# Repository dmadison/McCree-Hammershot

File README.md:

## Synopsis
These are the associated files for my McCree Hammershot controller project! I turned a Nerf revolver into a custom controller for the character of [McCree](https://playoverwatch.com/en-us/heroes/mccree/) in *Overwatch*. The revolver contains an Arduino Pro Micro, an MPU-6050 IMU, and a host of other parts to handle McCree's controls. When paired with either a DDR dance pad or a Wii Nunchuk to handle his movement, I can use all of McCree's controls and play the game reasonably well.

For more information, check out the full build log on [PartsNotIncluded.com](http://www.partsnotincluded.com/projects/mccree-hammershot-controller/).

## Dependencies
The Hammershot program is dependent on the [CapacitiveSensor](https://github.com/PaulStoffregen/CapacitiveSensor/releases/tag/0.5.1), [Encoder](https://github.com/PaulStoffregen/Encoder/releases/tag/1.4.1) and [FastLED](https://github.com/FastLED/FastLED/releases/tag/v3.1.6) libraries. The Nunchuk code is dependent on the [WiiChuck](https://github.com/madhephaestus/WiiChuck/releases/tag/0.0.23) library to handle communication between the board and the Nunchuk. Both sketches are dependent on the Arduino IDE's built-in Keyboard, Mouse, and Wire libraries. The sketches were compiled using version 1.8.2 of the IDE.

I've linked to the specific library releases that work with this code. Note that future versions may not be compatible.

## License
The Arduino code, CAD files, and breakout PCB are licensed under the terms of the [GNU General Public License v3.0](https://www.gnu.org/licenses/gpl-3.0.en.html).

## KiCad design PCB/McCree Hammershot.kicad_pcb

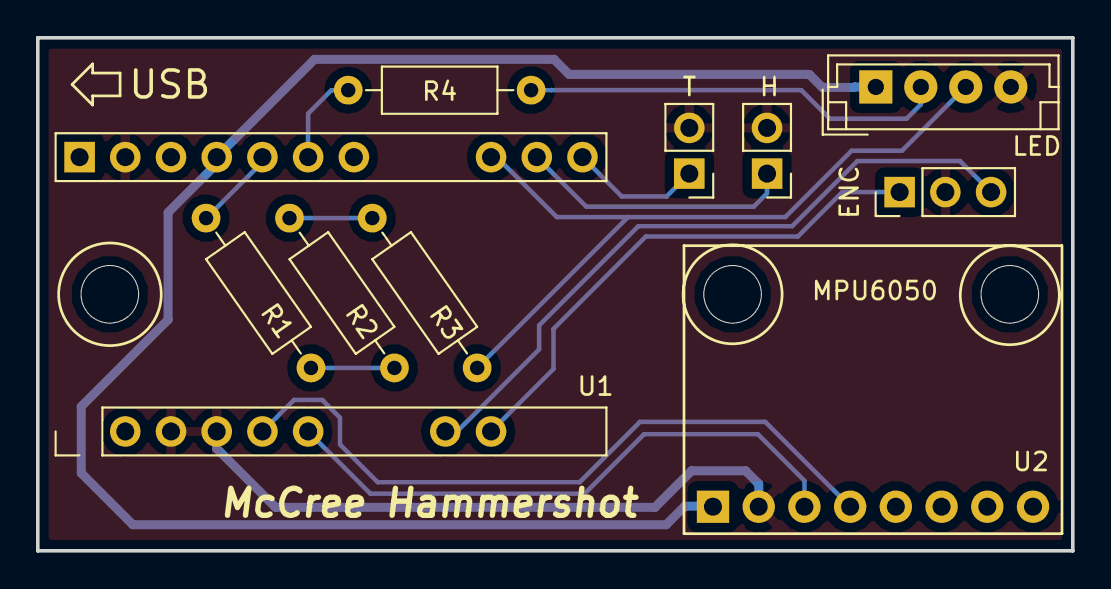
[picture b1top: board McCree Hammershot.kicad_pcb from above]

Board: 4 copper layers, 57.5 x 28.5 mm, 10 parts (0 on the bottom side), 14 nets.

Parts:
ENC: Rotary Enc. Conn; Pin_Header_Straight_1x03_Pitch2.54mm
H: Hammer Conn; Pin_Header_Straight_1x02_Pitch2.54mm
LED: LED Conn; JST_EH_B04B-EH-A_04x2.50mm_Straight
R1, R2, R3: 1M; R_Axial_DIN0207_L6.3mm_D2.5mm_P10.16mm_Horizontal
R4: 470; R_Axial_DIN0207_L6.3mm_D2.5mm_P10.16mm_Horizontal
T: Trigger Conn; Pin_Header_Straight_1x02_Pitch2.54mm
U1: Arduino_Pro-Micro; Arduino_Pro-Micro_Headers_Gaps
U2: MPU6050; MPU6050_Breakout

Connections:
/+5V: LED.1, U1.VCC, U2.1
/CapSense: LED.3, R3.1, U1.14
/CapSource: R1.2, U1.A3
/EncoderA: ENC.1, U1.7
/EncoderB: ENC.3, U1.6
/GND: ENC.2, H.2, LED.4, T.2, U1.GND, U2.2
/Hammer: H.1, U1.16
/LED_Data: LED.2, R4.1
/SCL: U1.3, U2.3
/SDA: U1.2, U2.4
/Trigger: T.1, U1.10
unnamed: R1.1, R2.2
unnamed: R2.1, R3.2
unnamed: R4.2, U1.A2

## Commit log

2017-11-12 Added license
2017-11-24 Removed I2C speed change
2017-11-24 Updated to most recent version of wiichuck
    0.0.21 -> 0.0.23
2017-11-24 Added connection check and release
